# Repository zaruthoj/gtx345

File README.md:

# Simulated Garmin GTX345 Transponder

This is a simulated Garmin GTX345 Transponder I designed for my home simulator. So far it's working well for me!  I've attempted to match the real unit as exactly as possible using commonly available tools and materials.

## Status

The hardware is complete and functional.  The softare is still a work in progress, though the major UI and sim connection features are done.

I've got 4 extra PCBs in hand.  Contact zaruthoj at gmail if you want one.  I'd be happy to sell them for $10 each plus shipping.

### TODO

* Add timer pages
* Add altitude alerting pages
* Add support for saving settings to EEPROM

## Assembly

* [BOM](doc/bom.md)
* Soldering (coming soon)
* [3D Printing](doc/printing.md)
* [Finishing](doc/finishing.md)
* Final Assembly (coming soon)

## Compatibility

I'm using this with P3Dv3 running the [PilotEdge](https://www.pilotedge.net/) Client and FSUIPC.  Additional work would be required to interface this with XPlane.  However, I've designed this in a modular way such that it should be straightforward to implement an XPlane interface.

## Equipment

### Required

* 3D Printer
* Soldering Iron
* 100, 200, and 400 grit sandpaper.

### Recommended

* Soldering Hot Air or Reflow (It's possible to use an iron on these SMD components, but is much harder.)
* Dremel with 100 and 200 grit sanding bits.  For sanding the recessed area around the screen.
* 100 grit diamond needle files.  For sanding the recessed area around the screen.

### Optional

* Random Orbital Sander.  This makes sanding the face and sides so much faster.
* XTC-3D 3d print coating.  If there are larger defects in the face of your print, this stuff works wonders.  I used it to fill in some areas around the circular buttons that failed to print correctly.

## Skills Required

* 3D printing
* SMD and thru hole soldering.
* Basic familiarity with uploading software to Arduinos.

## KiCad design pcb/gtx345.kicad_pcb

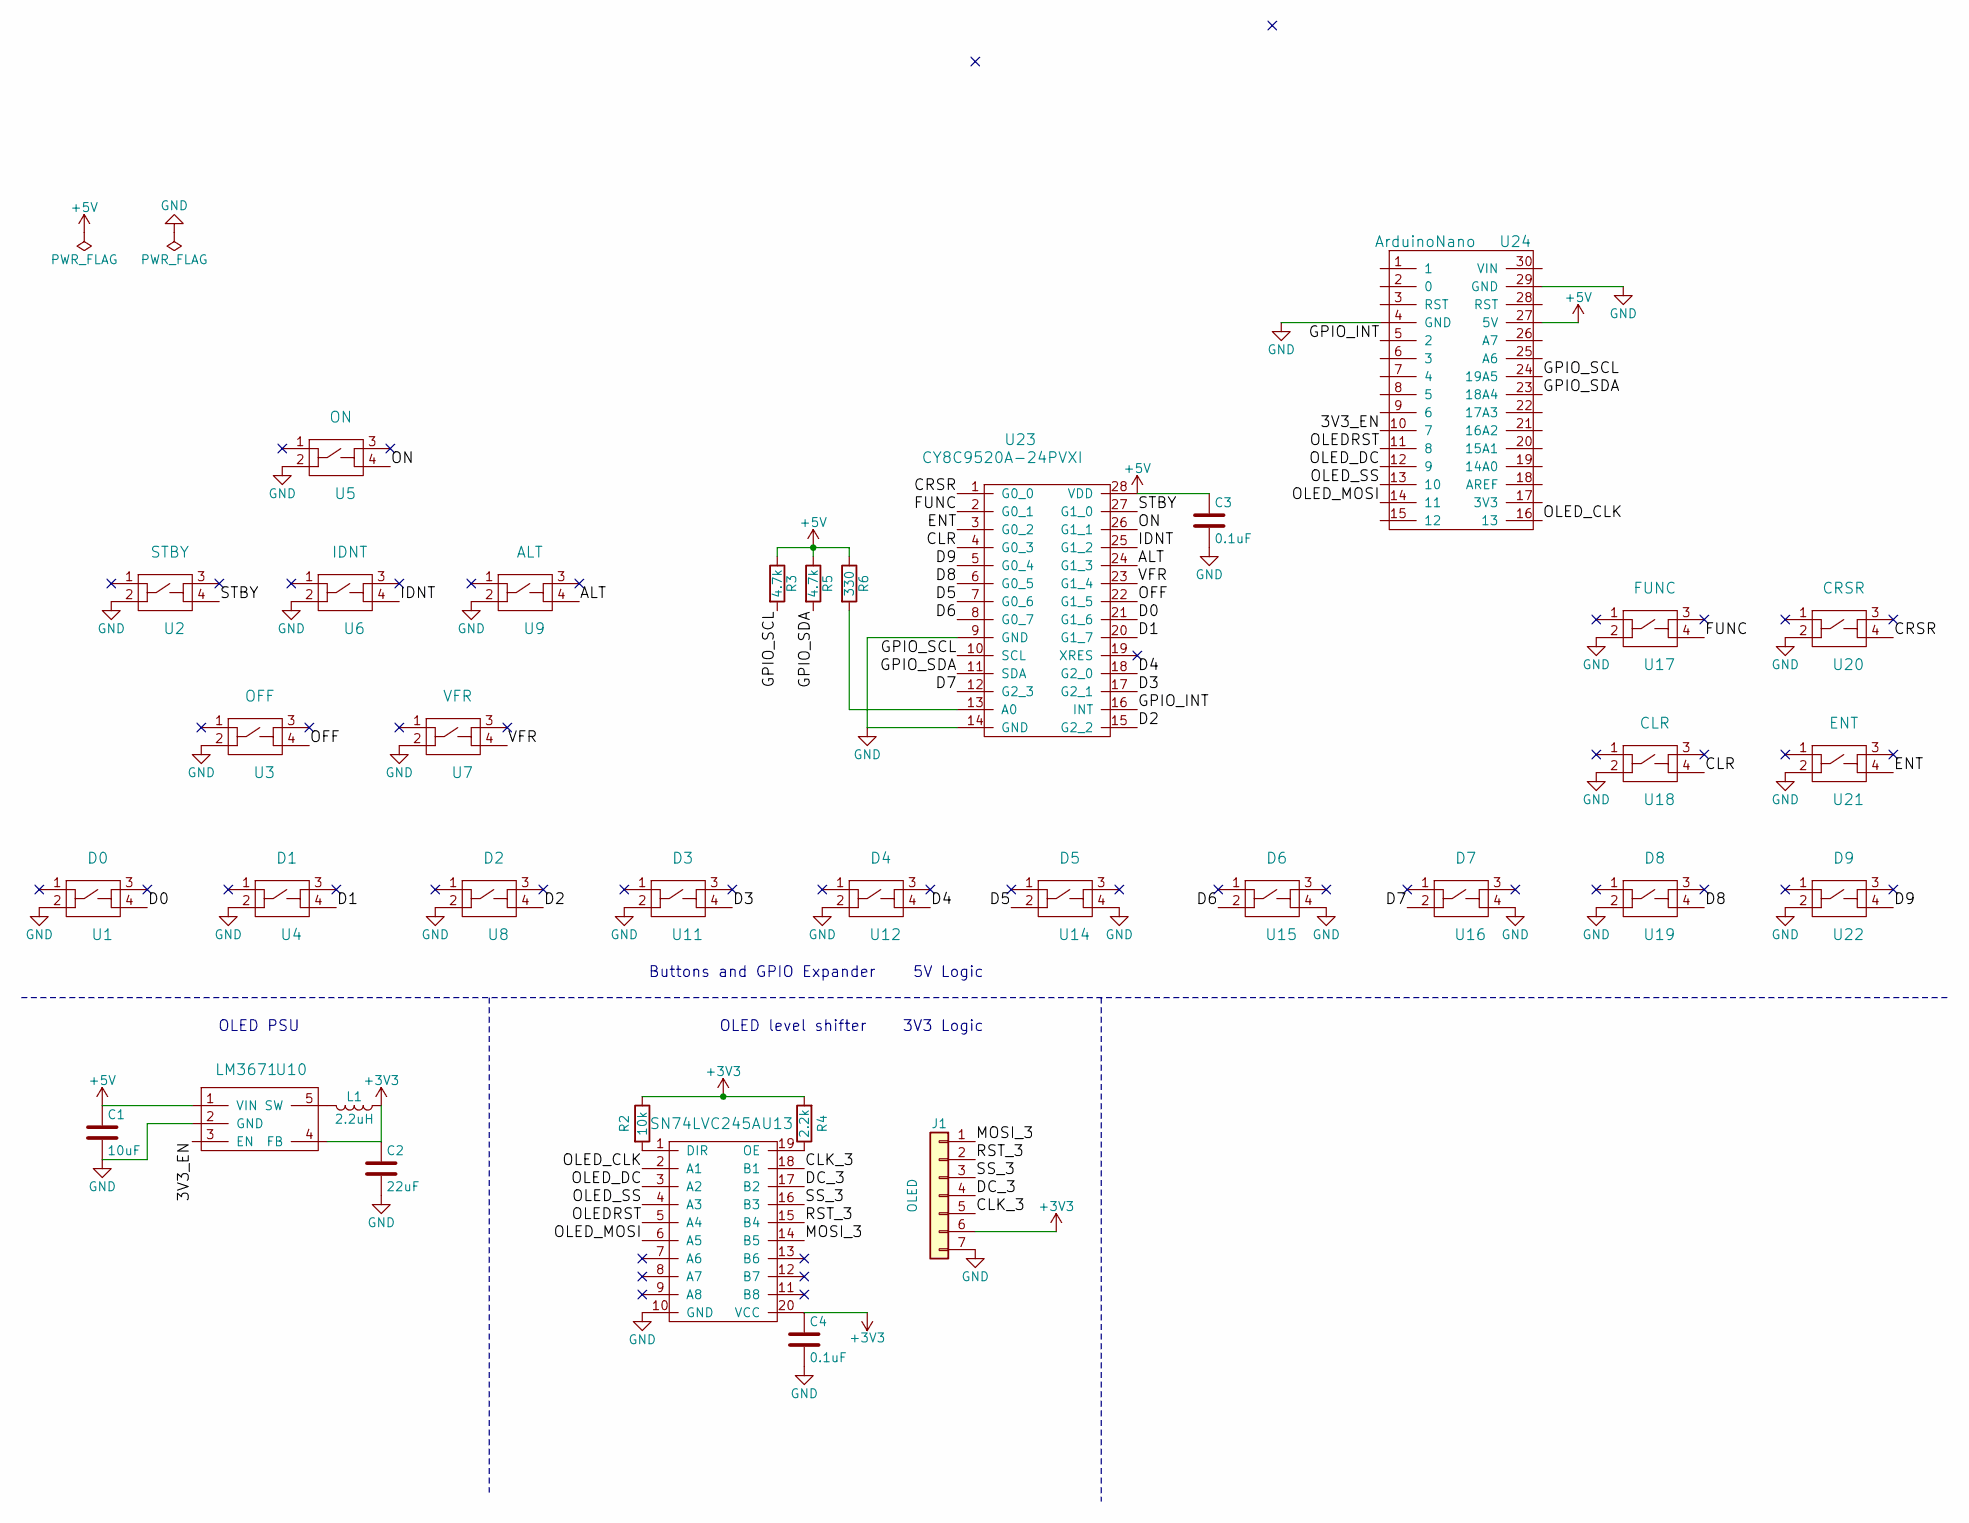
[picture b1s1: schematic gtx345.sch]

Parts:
C1: 10uF; C_0805_HandSoldering
C2: 22uF; C_0805_HandSoldering
C3, C4: 0.1uF; C_0805_HandSoldering
J1: OLED; Pin_Header_Straight_1x07_Pitch2.54mm
L1: 2.2uH; Inductor_NRH2412
R2: 10k; R_0805_HandSoldering
R3, R5: 4.7k; R_0805_HandSoldering
R4: 2.2k; R_0805_HandSoldering
R6: 330; R_0805_HandSoldering
U1: D0; Nidec_TR1_Button
U2: STBY; Nidec_TR1_Button
U3: OFF; Nidec_TR1_Button
U4: D1; Nidec_TR1_Button
U5: ON; Nidec_TR1_Button
U6: IDNT; Nidec_TR1_Button
U7: VFR; Nidec_TR1_Button
U8: D2; Nidec_TR1_Button
U9: ALT; Nidec_TR1_Button
U10: LM3671; SOT-23-5_HandSoldering
U11: D3; Nidec_TR1_Button
U12: D4; Nidec_TR1_Button
U13: SN74LVC245A; SOIC-20W_5.3x12.8mm_Pitch1.27mm
U14: D5; Nidec_TR1_Button
U15: D6; Nidec_TR1_Button
U16: D7; Nidec_TR1_Button
U17: FUNC; Nidec_TR1_Button
U18: CLR; Nidec_TR1_Button
U19: D8; Nidec_TR1_Button
U20: CRSR; Nidec_TR1_Button
U21: ENT; Nidec_TR1_Button
U22: D9; Nidec_TR1_Button
U23: CY8C9520A-24PVXI; 28_SSOP
U24: ArduinoNano; Arduino_Nano

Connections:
+3V3: C2.1, C4.1, J1.6, L1.1, R2.1, R4.2, U10.4 (FB), U13.20 (VCC)
+5V: C1.1, C3.1, R3.1, R5.1, R6.1, U10.1 (VIN), U23.28 (VDD), U24.27 (5V)
/3V3_EN: U10.3 (EN), U24.10 (7)
/ALT: U9.4, U23.24 (G1_3)
/CLK_3: J1.5, U13.18 (B1)
/CLR: U18.4, U23.4 (G0_3)
/CRSR: U20.4, U23.1 (G0_0)
/D0: U1.4, U23.21 (G1_6)
/D1: U4.4, U23.20 (G1_7)
/D2: U8.4, U23.15 (G2_2)
/D3: U11.4, U23.17 (G2_1)
/D4: U12.4, U23.18 (G2_0)
/D5: U14.2, U23.7 (G0_6)
/D6: U15.2, U23.8 (G0_7)
/D7: U16.2, U23.12 (G2_3)
/D8: U19.4, U23.6 (G0_5)
/D9: U22.4, U23.5 (G0_4)
/DC_3: J1.4, U13.17 (B2)
/ENT: U21.4, U23.3 (G0_2)
/FUNC: U17.4, U23.2 (G0_1)
/GPIO_INT: U23.16 (INT), U24.5 (2)
/GPIO_SCL: R3.2, U23.10 (SCL), U24.24 (19A5)
/GPIO_SDA: R5.2, U23.11 (SDA), U24.23 (18A4)
/IDNT: U6.4, U23.25 (G1_2)
/MOSI_3: J1.1, U13.14 (B5)
/OFF: U3.4, U23.22 (G1_5)
/OLEDRST: U13.5 (A4), U24.11 (8)
/OLED_CLK: U13.2 (A1), U24.16 (13)
/OLED_DC: U13.3 (A2), U24.12 (9)
/OLED_MOSI: U13.6 (A5), U24.14 (11)
/OLED_SS: U13.4 (A3), U24.13 (10)
/ON: U5.4, U23.26 (G1_1)
/RST_3: J1.2, U13.15 (B4)
/SS_3: J1.3, U13.16 (B3)
/STBY: U2.4, U23.27 (G1_0)
/VFR: U7.4, U23.23 (G1_4)
GND: C1.2, C2.2, C3.2, C4.2, J1.7, U1.2, U2.2, U3.2, U4.2, U5.2, U6.2, U7.2, U8.2, U9.2, U10.2 (GND), U11.2, U12.2, U13.10 (GND), U14.4, U15.4, U16.4, U17.2, U18.2, U19.2, U20.2, U21.2, U22.2, U23.9 (GND), U23.14 (GND), U24.4 (GND), U24.29 (GND)
unnamed: L1.2, U10.5 (SW)
unnamed: R2.2, U13.1 (DIR)
unnamed: R4.1, U13.19 (OE)
unnamed: R6.2, U23.13 (A0)

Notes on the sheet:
Buttons and GPIO Expander
5V Logic
OLED level shifter
3V3 Logic
OLED PSU

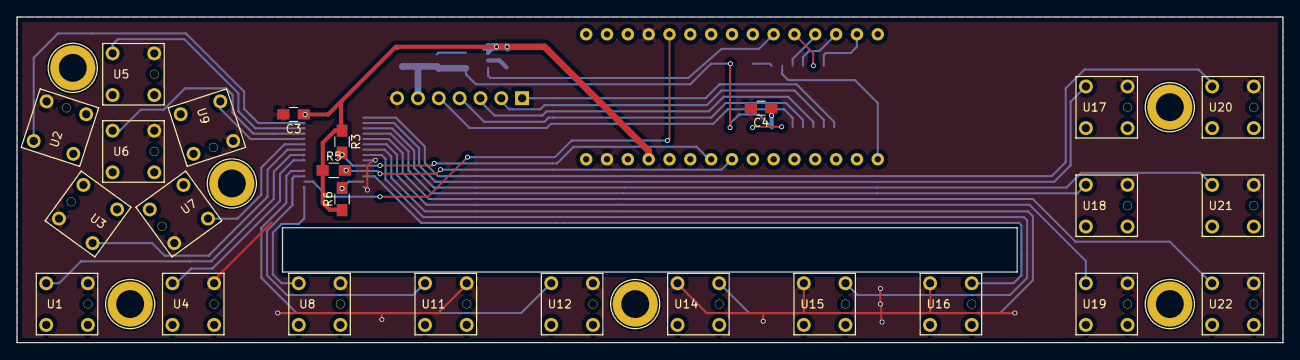
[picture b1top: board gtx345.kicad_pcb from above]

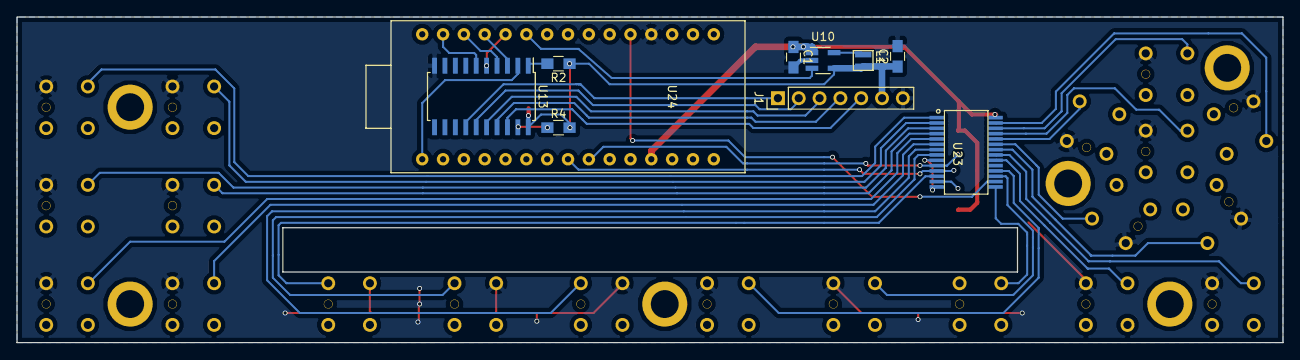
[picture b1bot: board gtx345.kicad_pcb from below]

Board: 2 copper layers, 154.4 x 39.7 mm, 41 parts (10 on the bottom side), 41 nets.

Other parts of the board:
Ref**: Val**; SCREW_M3
Ref**#2, Ref**#3, Ref**#4, Ref**#5, Ref**#6: Val**; SCREW_M3

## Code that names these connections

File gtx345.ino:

#include <Wire.h>
#include <Arduino.h>
#include <SPI.h>
#include <U8g2lib.h>
#include "listener.h"
#include "catalog.h"

#define REG_INPUT_PORT_START 0x00
#define REG_OUTPUT_PORT_START 0x08
#define REG_INT_STATUS_START 0x10
#define REG_PORT_SELECT 0x18
#define REG_INT 0x19
#define REG_PORT_DIRECTION 0x1C
#define REG_PULL_UP 0x1D
#define NUM_PORTS 3

#define ENABLE_3V3_PIN 7

#define OLED_RESET 8
#define OLED_DC 9
#define OLED_CS 10
#define OLED_MOSI 11
#define OLED_CLK 13

Controller &controller(bool reset=false) {
  static U8G2_SSD1322_NHD_256X64_1_4W_HW_SPI screen(U8G2_R2, OLED_CS, OLED_DC, OLED_RESET);
  static Controller controller(&screen);
  return controller;
}

void isr();

class CY8C95x0A {
 public:
  CY8C95x0A(uint8_t i2c_address, int interrrupt_pin) :
    interrrupt_pin_(interrrupt_pin),
    i2c_address_(i2c_address),
    triggered_(false) {}

  void check_error(int error) {
    if (error != 0) {
      Serial.print("I2C Error: ");
      Serial.println(error);
    }
  }
  
  void write_reg(uint8_t reg_offset, uint8_t value) {
    Wire.beginTransmission(i2c_address_);
    Wire.write(reg_offset);
    //check_error(Wire.endTransmission(false));
    Wire.write(value);
    check_error(Wire.endTransmission(true));

    delayMicroseconds(100);
    uint8_t check_value = read_reg(reg_offset);
    while(check_value != value) {
      Serial.print("Register ");
      Serial.print(reg_offset);
      Serial.print(" = ");
      Serial.print(check_value);
      Serial.print(". Wrote ");
      Serial.println(value);
      delay(1000);
      check_value = read_reg(reg_offset);
    }
    delayMicroseconds(100);
  }
  
  void read_regs(uint8_t reg_offset, uint8_t num_bytes, uint8_t * output) {
    Wire.beginTransmission(i2c_address_);
    Wire.write(reg_offset);
    check_error(Wire.endTransmission(false));
    Wire.requestFrom(i2c_address_, num_bytes, (uint8_t)true);
    for (int i = 0; i < num_bytes; ++i) {
      output[i] = Wire.read();
    }
  }

  uint8_t read_reg(uint8_t reg_offset) {
    Wire.beginTransmission(i2c_address_);
    Wire.write(reg_offset);
    check_error(Wire.endTransmission(false));
    Wire.requestFrom(i2c_address_, 1, (uint8_t)true);
    uint8_t val = Wire.read();
    return val;
  }

  void scan() {
    if (!triggered_) return;

    uint8_t int_status[NUM_PORTS];
    uint8_t values[NUM_PORTS];
    read_regs(REG_INT_STATUS_START, NUM_PORTS, int_status);
    read_regs(REG_INPUT_PORT_START, NUM_PORTS, values);
    triggered_ = false;
    int_status[2] &= 0x0F;
    for (int i = 0; i < NUM_PORTS; ++i) {
      int changed = -1;
      switch(int_status[i]) {
        case 0x01:
          changed = 0;
          break;
        case 0x02:
          changed = 1;
          break;
        case 0x04:
          changed = 2;
          break;
        case 0x08:
          changed = 3;
          break;
        case 0x10:
          changed = 4;
          break;
        case 0x20:
          changed = 5;
          break;
        case 0x40:
          changed = 6;
          break;
        case 0x80:
          changed = 7;
          break;
        default:
          continue;
      }
      controller().on_event(i << 4 | changed, (int_status[i] & ~values[i]) != 0);
    }
  }
  
  void begin() {
    Wire.begin();
    attachInterrupt(digitalPinToInterrupt(interrrupt_pin_), isr, RISING);
    for(uint8_t port_num = 0; port_num < NUM_PORTS; ++port_num) {
      write_reg(REG_OUTPUT_PORT_START + port_num, 0);
      write_reg(REG_PORT_SELECT, port_num);
      write_reg(REG_PORT_DIRECTION, 0xff);
      write_reg(REG_PULL_UP, 0xff);
      if (port_num != 2) {
        write_reg(REG_INT, 0x00);
      } else {
        write_reg(REG_INT, 0xF0);
      }
    }
  }

  volatile bool triggered_;
 private:
  int interrrupt_pin_;
  uint8_t i2c_address_;
};


CY8C95x0A expander(0x21, 2);
void isr() {
  expander.triggered_ = true;
}


StatusPage &status_page() {
  static StatusPage internal;
  return internal;
}
SquawkDisplay &squawk_display() {
  static SquawkDisplay internal;
  return internal;
}

StaticText &alt_mode() {
  static StaticText internal("ALT", ALT_X, ALT_Y, ALT_FONT);
  return internal;
}
IdentText &ident_text() {
  static IdentText internal("IDNT", IDNT_X, IDNT_Y, IDNT_FONT);
  return internal;
}
FunctionGroup &xpdr_group() {
  static FunctionGroup internal;
  return internal;
}
FlightId &flight_id() {
  static FlightId internal;
  return internal;
}
FlightIdEdit &flight_id_edit() {
  static FlightIdEdit internal;
  return internal;
}
SerialCom &serial_com() {
  static SerialCom internal;
  return internal;
}

void setup() {
  Serial.begin(115200);
  expander.begin();
  pinMode(ENABLE_3V3_PIN, OUTPUT);
  digitalWrite(ENABLE_3V3_PIN, HIGH);

  controller().add_child(&status_page(), true);
  controller().add_child(&ident_text(), true);
  controller().add_child(&flight_id_edit(), false);
  controller().add_child(&serial_com(), true);
  
  status_page().add_child(&alt_mode(), true);
  status_page().add_child(&squawk_display(), true);
  status_page().add_child(&xpdr_group(), true);

  xpdr_group().add_function(&flight_id());

  controller().begin();
  controller().on_event(EVENT_RENDER);
}

uint32_t last_refresh_ms = 0;
void loop() {
  expander.scan();

  controller().process_event();
  uint32_t now_ms = millis();
  if (now_ms > last_refresh_ms + 100) {
    last_refresh_ms = now_ms;
    controller().on_event(EVENT_TICK);
  }
}

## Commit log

2019-01-26 labels
2019-01-26 LCD and basic UI mostly working with unit tests.
2019-01-29 Added serial coms
2019-01-29 Removing ready message
2019-01-29 Working with sim!
2019-02-02 Fixed screen size issues, moved gerber files, and added documentation.
2019-02-02 Fix link
2019-02-02 Fix BOM formatting
2019-02-02 Added STL models, labels pdf, and finishing and printing docs.
2019-02-02 Added printing doc link.
